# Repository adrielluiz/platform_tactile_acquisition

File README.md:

# Dynamic Tactile Data Acquisition Platform

### Overview

This repository hosts a Dynamic Tactile Data Acquisition Platform,  designed to facilitate tactile experiments across two axes (X and Z). It is a versatile tool aimed at researchers and engineers involved in tactile data collection and analysis.

### Features

- **Two-Axis Movement**: Precision-engineered to operate along both X and Z axes, ensuring comprehensive coverage for tactile experiments.
- **Dual Stepper Motors**: Employs two robust stepper motors, delivering smooth and accurate motion control.
- **Microcontroller**: Utilizes an STM32F401 MCU.
- **Integrated System Components**:
  - **Firmware**: C/C++ firmware for platform control.
  - **Software Interface**: A user-friendly Python-based software interface for movement planning and execution.
  - **Serial Communication**: Seamless serial communication protocol linking the software and firmware components.

### Repository Contents

- **Mechanical Structure 3D Files**: Detailed 3D models of the platform's mechanical structure for easy replication or modification.
- **Firmware Variants**: Two distinct firmware versions tailored to different stepper motor drivers.
- **Control Software**: Intuitive software designed for seamless interaction with the microcontroller unit.
- **PCB Design and Layout Files**: Comprehensive files for the printed circuit board (PCB) design.

### Getting Started

Please refer to the individual folders.

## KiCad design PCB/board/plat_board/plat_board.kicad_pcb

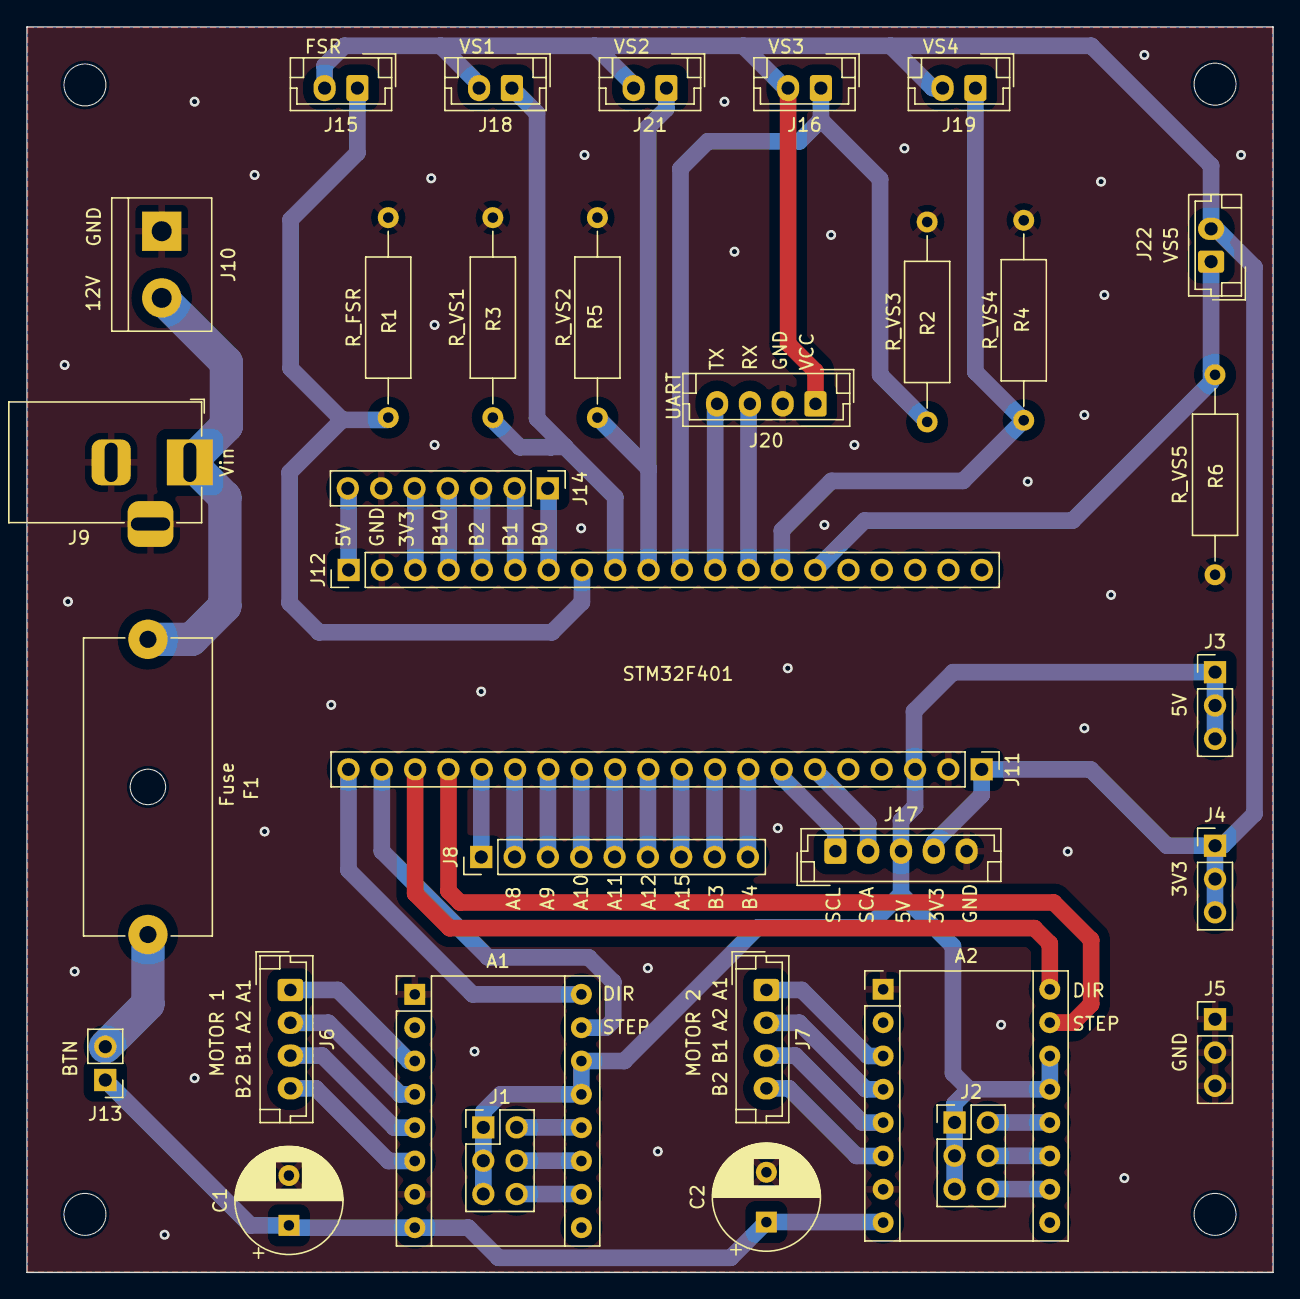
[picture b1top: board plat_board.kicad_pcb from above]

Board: 2 copper layers, 95.0 x 94.9 mm, 37 parts (0 on the bottom side), 49 nets.

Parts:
A1, A2: Pololu_Breakout_DRV8825; Pololu_Breakout-16_15.2x20.3mm
C1, C2: 100uF; CP_Radial_D8.0mm_P3.80mm
F1: Fuse; Fuseholder_Cylinder-5x20mm_Schurter_0031_8201_Horizontal_Op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
H1, H2, H3, H4: MountingHole; MountingHole_3.2mm_M3
J1: Step_Select1; PinHeader_2x03_P2.54mm_Vertical
J2: Step_Select2; PinHeader_2x03_P2.54mm_Vertical
J3: Conn_Ex_5V; PinHeader_1x03_P2.54mm_Vertical
J4: Conn_Ex_3v3; PinHeader_1x03_P2.54mm_Vertical
J5: Conn_Ext_GND; PinHeader_1x03_P2.54mm_Vertical
J6: MOTOR1; JST_EH_B4B-EH-A_1x04_P2.50mm_Vertical
J7: MOTOR2; JST_EH_B4B-EH-A_1x04_P2.50mm_Vertical
J8: Conn_Extra; PinHeader_1x09_P2.54mm_Vertical
J9: Font; BarrelJack_Horizontal
J10: VIN; TerminalBlock_bornier-2_P5.08mm
J11, J12: STM32F4; PinHeader_1x20_P2.54mm_Vertical
J13: Btn_OnOff; PinHeader_1x02_P2.54mm_Vertical
J14: Conn_Ext2; PinHeader_1x07_P2.54mm_Vertical
J15: FSR; JST_EH_B2B-EH-A_1x02_P2.50mm_Vertical
J16: VS3; JST_EH_B2B-EH-A_1x02_P2.50mm_Vertical
J17: MPU; JST_EH_B5B-EH-A_1x05_P2.50mm_Vertical
J18: VS1; JST_EH_B2B-EH-A_1x02_P2.50mm_Vertical
J19: VS4; JST_EH_B2B-EH-A_1x02_P2.50mm_Vertical
J20: UART; JST_EH_B4B-EH-A_1x04_P2.50mm_Vertical
J21: VS2; JST_EH_B2B-EH-A_1x02_P2.50mm_Vertical
J22: VS5; JST_EH_B2B-EH-A_1x02_P2.50mm_Vertical
R1: R_FSR; R_Axial_DIN0309_L9.0mm_D3.2mm_P15.24mm_Horizontal
R2: R_VS3; R_Axial_DIN0309_L9.0mm_D3.2mm_P15.24mm_Horizontal
R3: R_VS1; R_Axial_DIN0309_L9.0mm_D3.2mm_P15.24mm_Horizontal
R4: R_VS4; R_Axial_DIN0309_L9.0mm_D3.2mm_P15.24mm_Horizontal
R5: R_VS2; R_Axial_DIN0309_L9.0mm_D3.2mm_P15.24mm_Horizontal
R6: R_VS5; R_Axial_DIN0309_L9.0mm_D3.2mm_P15.24mm_Horizontal

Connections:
/3v3: J4.1, J4.2, J4.3, J11.1, J15.2, J16.2, J17.4, J18.2, J19.2, J20.1, J21.2, J22.2
/5V: A1.13 (~RST), A1.14 (~SLP), A2.13 (~RST), A2.14 (~SLP), J1.1, J1.3, J1.5, J2.1, J2.3, J2.5, J3.1, J3.2, J3.3, J11.3, J17.3
/12V: A1.8 (VMOT), A2.8 (VMOT), C1.1, C2.1, J13.1
/FSR: J12.8, J15.1, R1.2
/M0_1: A1.10 (M0), J1.6
/M0_2: A2.10 (M0), J2.6
/M1_DIR: A1.16 (DIR), J11.20
/M1_STEP: A1.15 (STEP), J11.19
/M2_1: A1.12 (M2), J1.2
/M2_2: A2.12 (M2), J2.2
/M2_DIR: A2.16 (DIR), J11.18
/M2_STEP: A2.15 (STEP), J11.17
/MPU_SCA: J11.6, J17.2
/MPU_SCL: J11.7, J17.1
/UART_RX: J12.12, J20.4
/UART_TX: J12.13, J20.3
/VS1: J12.9, J18.1, R3.2
/VS2: J12.10, J21.1, R5.2
/VS3: J12.11, J16.1, R2.2
/VS4: J12.14, J19.1, R4.2
/VS5: J12.15, J22.1, R6.2
/Vin: F1.1, J9.1, J10.2
GND: A1.1 (GND), A1.7 (GND), A2.1 (GND), A2.7 (GND), C1.2, C2.2, J5.1, J5.2, J5.3, J9.2, J9.3, J10.1, J11.2, J12.2, J14.6, J17.5, J20.2, R1.1, R2.1, R3.1, R4.1, R5.1, R6.1
unnamed: A1.4 (A1), J6.2
unnamed: A1.3 (A2), J6.1
unnamed: A1.5 (B1), J6.3
unnamed: A1.6 (B2), J6.4
unnamed: A1.11 (M1), J1.4
unnamed: A2.4 (A1), J7.2
unnamed: A2.3 (A2), J7.1
unnamed: A2.5 (B1), J7.3
unnamed: A2.6 (B2), J7.4
unnamed: A2.11 (M1), J2.4
unnamed: J8.9, J11.8
unnamed: J8.8, J11.9
unnamed: J8.7, J11.10
unnamed: J8.6, J11.11
unnamed: J8.5, J11.12
unnamed: J8.4, J11.13
unnamed: J8.3, J11.14
unnamed: J8.2, J11.15
unnamed: J8.1, J11.16
unnamed: J12.1, J14.7
unnamed: J12.3, J14.5
unnamed: J12.4, J14.4
unnamed: J12.5, J14.3
unnamed: J12.6, J14.2
unnamed: J12.7, J14.1
unnamed: F1.2, J13.2

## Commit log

2023-05-08 Adicionando firmware
2023-05-11 Adição de comandos
2023-06-17 Adding new files
2023-06-19 Correção de bugs no fw
2023-06-21 Término da primeira versão do fw
2023-06-22 Adicionando software demo
2023-06-22 Adição de componentes na gui
2023-06-22 Adicionando commandos da serial
2023-06-23 Atualizando gui
2023-06-25 Terminando 1 versão do sw
2023-06-26 Adição de dados para excel
2023-06-26 Adicionando interface de test
2023-06-27 Adicionando função de executar tafera repetidamente
2023-07-04 Adicionando o salvamento dos dados em excel e melhorando a interface
2023-07-27 Adicionando arquivos da nova PCB
2023-08-08 Adding image
2023-08-08 Adding firmware
2024-01-18 Improving fw v2
2024-01-18 fixing commit
2024-01-18 Removing unnecessary code
2024-01-23 Improving README.md
2024-01-29 Removing unecessary files
2024-01-29 Adding second serial to gui
2024-01-30 Improving gui
2024-02-05 Fixing gui
2024-02-22 Improving sw
